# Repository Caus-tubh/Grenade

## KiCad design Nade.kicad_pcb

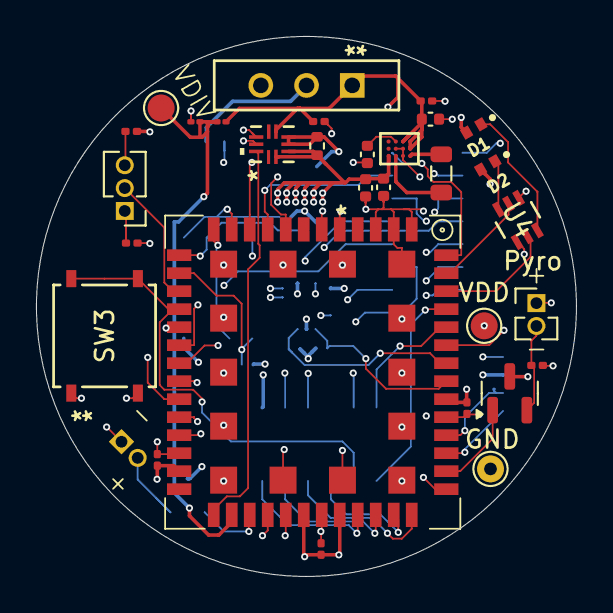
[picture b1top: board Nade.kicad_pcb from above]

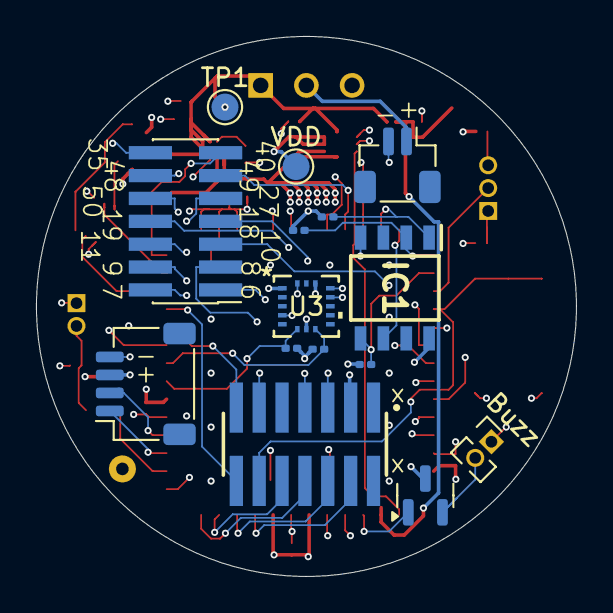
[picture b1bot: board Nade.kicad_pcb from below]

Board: 4 copper layers, 30.0 x 30.0 mm, 45 parts (15 on the bottom side), 50 nets.

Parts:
Buzz: Buzzer; PinHeader_1x02_P1.27mm_Vertical
C2, C3, C4: 100n; C_0201_0603Metric
C5: 10u; C_0402_1005Metric
C6, C10: 0.1u; C_0201_0603Metric
C7: 1u; C_0402_1005Metric
C8, C9: 22u; C_0402_1005Metric
D1, D2: EAST10052WA0; LEDC1005X25N
GND: GND; TestPoint_THTPad_D1.5mm_Drill0.7mm
IC1: MB85RS2MTYPNF-G-AWERE2; SOIC127P600X175-8N
J1: FTSH-107-01-L-DV-K; SAMTEC_FTSH-107-01-L-DV-K
J2: Conn_01x03_Pin; PinHeader_1x03_P1.27mm_Vertical
J3: Extra; PinHeader_2x07_P1.27mm_Vertical_SMD
J4: BATT; JST_SH_BM02B-SRSS-TB_1x02-1MP_P1.00mm_Vertical
J7: UART; JST_SH_SM04B-SRSS-TB_1x04-1MP_P1.00mm_Horizontal
L1: 1u; L_0805_2012Metric
MCU1: MAMWLE
Pyro: Conn_01x02_Pin; PinHeader_1x02_P1.27mm_Vertical
Q1, Q2: NMOS; SOT-23
R8, R9: 10k; R_0201_0603Metric
R10: 10m; R_0402_1005Metric
R11: 6.8k; R_01005_0402Metric
R12: 3.3k; R_01005_0402Metric
R13, R14, R15, R16, R17, R18: 4.7k; R_0201_0603Metric
SW2: SW_SPDT; switch
SW3: PTS526 SM15 SMTR2 LFS; SON4_PTS526 SM15 SMTR2 LFS_CNK
TP1: RAWV; TestPoint_Pad_D1.5mm
TP4: V_DIV; TestPoint_Pad_D1.5mm
U1: MP28160GC-Z; WLCSP-MNP
U2: INA213AIRSWR; INA213
U3: ADXL373BCCZ-RL7; ADXL373
U4: SSM6N7002KFU_LF; SOT-363 US6_TOS
VDD: VDD; TestPoint_Pad_D1.5mm
VDD#2: VDD; TestPoint_Pad_D1.5mm

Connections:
/PA1: IC1.6 (SCK), MCU1.52 (PA1)
/PA2: J1.14, MCU1.37 (PA2)
/PA3: J1.13, MCU1.36 (PA3)
/PA4: IC1.1 (~CS), MCU1.51 (PA4), R13.1
/PA6: IC1.2 (SO), MCU1.1 (PA6), R14.1
/PA7: IC1.5 (SI), MCU1.2 (PA7), R15.1
/PA10: MCU1.17 (PA10), Q1.2 (G)
/PA11: MCU1.16 (PA11), R11.1, R12.2, TP4.1
/PA13: J1.04, MCU1.23 (PA13)
/PA14: J1.06, MCU1.24 (PA14)
/PA15: J1.10, MCU1.25 (PA15)
/PB2: MCU1.15 (PB2), U2.10 (OUT)
/PB3: J1.08, MCU1.26 (PB3)
/PB5: MCU1.28 (PB5), Q2.2 (G)
/PB9: MCU1.39 (PB9), U4.2 (GATE1)
/PB15: MCU1.38 (PB15), U4.5 (GATE2)
/PC0: MCU1.34 (PC0), R16.1, U3.8 (*CS/SCL)
/PC1: MCU1.33 (PC1), R17.1, U3.6 (MOSI/SDA)
GND: Buzz.1, C2.1, C3.1, C4.1, C5.2, C6.2, C7.1, C8.2, C9.2, C10.2, GND.1, IC1.4 (VSS), J1.05, J1.07, J1.11, J4.2, J7.4, MCU1.5 (GND), MCU1.12 (GND), MCU1.21 (GND), MCU1.31 (GND), MCU1.41 (GND), MCU1.42 (GND), MCU1.43 (GND), MCU1.45 (GND), MCU1.46 (GND), MCU1.53 (GND), MCU1.54 (GND), MCU1.55 (GND), MCU1.56 (GND), MCU1.57 (GND), MCU1.58 (GND), MCU1.59 (GND), MCU1.60 (GND), MCU1.61 (GND), MCU1.62 (GND), MCU1.63 (GND), MCU1.64 (GND), MCU1.65 (GND), MCU1.66 (GND), Pyro.1, R9.1, R12.1, R18.2, SW3.1, SW3.2, U1.B2 (AGND), U1.B3 (GND), U1.C2 (EN), U2.8 (REF), U2.9 (GND), U3.4 (SCLK), U3.12 (GND), U3.13 (GND), U3.16 (GND), U4.1 (SOURCE1), U4.4 (SOURCE2)
unnamed: J2.1, R9.2
unnamed: J2.2, MCU1.3 (BOOT0)
unnamed: J2.3, R8.2
unnamed: J3.1, MCU1.6 (PA9)
unnamed: J3.2, MCU1.7 (PC13)
unnamed: J3.3, MCU1.8 (PB11)
unnamed: J3.4, MCU1.9 (PB10)
unnamed: J3.5, MCU1.10 (PB12)
unnamed: J3.6, MCU1.11 (PB13)
unnamed: J3.7, MCU1.18 (PA12)
unnamed: J3.8, MCU1.19 (PB14)
unnamed: J3.9, MCU1.27 (PB4)
unnamed: J3.10, MCU1.50 (PA5)
unnamed: J3.11, MCU1.49 (PA8)
unnamed: J3.12, MCU1.48 (PC2)
unnamed: J3.13, MCU1.40 (PB8)
unnamed: J3.14, MCU1.35 (PC6)
unnamed: J4.1, SW2.2 (B)
unnamed: Pyro.2, Q2.3 (S), R18.1
unnamed: J7.1, MCU1.29 (PB6)
unnamed: J7.2, MCU1.30 (PB7)
unnamed: Buzz.2, Q1.3 (S)
unnamed: R10.1, U2.4 (IN-), U2.5 (IN-), VDD#2.1
unnamed: C5.1, C6.1, C10.1, R11.2, SW2.1 (A), TP1.1, U1.A1 (IN), U1.A2 (IN), U1.B1 (IN), U2.6 (V+)
unnamed: L1.1, U1.A3 (SW1)
unnamed: L1.2, U1.C3 (SW2)
unnamed: C7.2, U1.C1 (VCC)
unnamed: D1.C, U4.6 (DRAIN1)
unnamed: D2.C, U4.3 (DRAIN2)
RESET': J1.12, MCU1.4 (RESET), SW3.3, SW3.4
VDD: C2.2, C3.2, C4.2, C8.1, C9.1, D1.A, D2.A, IC1.8 (VDD), J1.03, J7.3, MCU1.13 (VDD), MCU1.20 (VREF+), MCU1.22 (VDD), MCU1.32 (VDD), Q1.1 (D), Q2.1 (D), R8.1, R10.2, R13.2, R14.2, R15.2, R16.2, R17.2, U1.D3 (OUT), U2.2 (IN+), U2.3 (IN+), U3.1 (VDD_I/O), U3.7 (MISO), U3.14 (VS), VDD.1

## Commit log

2025-11-10 initialization
